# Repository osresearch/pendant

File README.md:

Bootloader
===

The ATtiny85 needs to be flashed with a bootloader before it can
be programmed with the Arduino IDE.  This requires extra hardware,
such as a teensy or arduino configured as an ISP.

The bootloader is then flashed via an SOIC socket.  It is possible to
via a chip clip, but this seems to be somewhat flakey due to the
charlieplexing matrix.

Using the arduino IDE, select "`File`-`Examples`-`11. Arduino ISP`"
and set the "`Tools`-`Board`" for whatever type of arduino or teensy you 
are using.  For a teensy the minimum pinout is:

	Teensy	SOIC	Use
	Vcc	8
	GND	4
	1	7	SCK
	2	5	MOSI
	3	6	MISO
	10	1	Reset

Clone the bootloader tree:

    git clone https://github.com/osresearch/gemma-bootloader

You might have to edit the `gemma-bootloader/Makefile` to have the
right path to your Arduino build environment and `avrdude` tool.  You will
likely have to edit it to set the serial device that your Teensy or
Arduino shows up as.

Connect the ArduinoISP to the ATtiny85 and flash the bootloader:

    make -C gemma-bootloader flash_lv

This should result in an ok message.  if it doesn't, check the connections
and try again.  If it is succesful you won't be able to reflash it,
since the reset pin is disabled.

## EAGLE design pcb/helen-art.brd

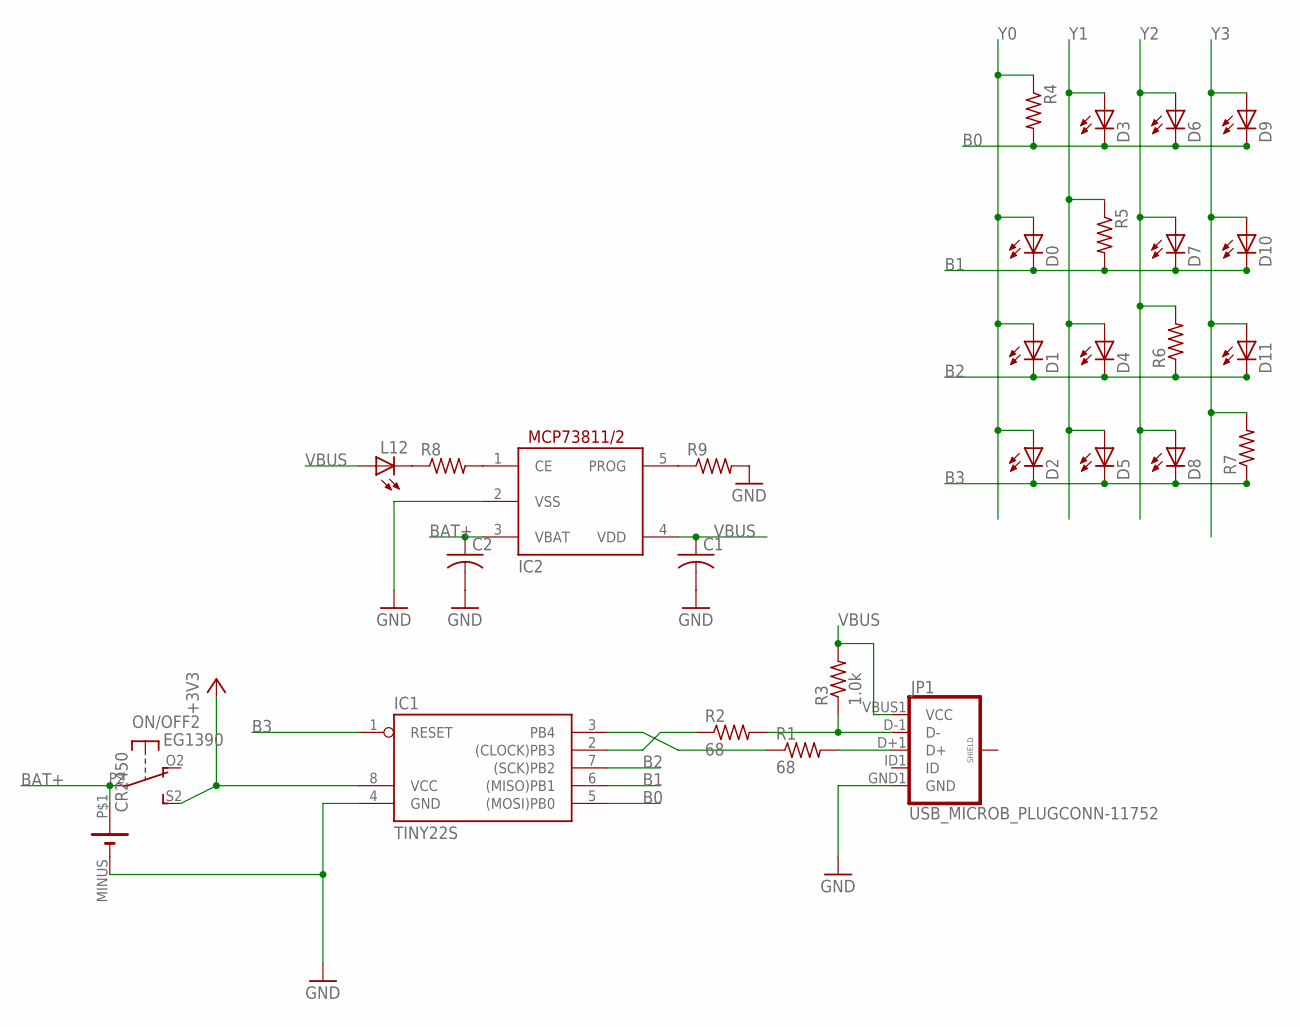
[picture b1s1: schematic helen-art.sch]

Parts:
C1, C2: C-USC0603; C0603
D0, D1, D2, D3, D4, D5, D6, D7, D8, D9, D10, D11: LEDCHIPLED_0805; CHIPLED_0805
IC1: TINY22S; SOIC8
IC2: MCP73811/2; SOT23-5L
JP1: USB_MICROB_PLUGCONN-11752; USB-B-MICRO-SMD_V03
L12: LEDCHIPLED_0805; CHIPLED_0805
ON/OFF: EG1390
R1, R2: 68; R0603
R3: 1.0k; R0603
R4, R5, R6, R7, R8, R9: R-US_R0603; R0603
U$3: CR2450; CR2450_KEYSTONE

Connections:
+3V3: IC1.8 (VCC), ON/OFF.S2 (S)
B0: D3.C, D6.C, D9.C, IC1.5 ((MOSI)PB0), R4.2
B1: D0.C, D7.C, D10.C, IC1.6 ((MISO)PB1), R5.2
B2: D1.C, D4.C, D11.C, IC1.7 ((SCK)PB2), R6.1
B3: D2.C, D5.C, D8.C, IC1.1 (RESET), R7.1
BAT+: C2.1, IC2.3 (VBAT), ON/OFF.P2, U$3.P$1 (+)
GND: C1.2, C2.2, IC1.4 (GND), IC2.2 (VSS), JP1.GND1 (GND), R9.2, U$3.MINUS (-)
unnamed: JP1.D+1 (D+), R1.2
unnamed: JP1.D-1 (D-), R2.2, R3.1
unnamed: IC1.3 (PB4), R1.1
unnamed: IC1.2 ((CLOCK)PB3), R2.1
unnamed: IC2.5 (PROG), R9.1
unnamed: IC2.1 (CE), R8.2
unnamed: L12.C, R8.1
VBUS: C1.1, IC2.4 (VDD), JP1.VBUS1 (VCC), L12.A, R3.2
Y0: D0.A, D1.A, D2.A, R4.1
Y1: D3.A, D4.A, D5.A, R5.1
Y2: D6.A, D7.A, D8.A, R6.2
Y3: D9.A, D10.A, D11.A, R7.2

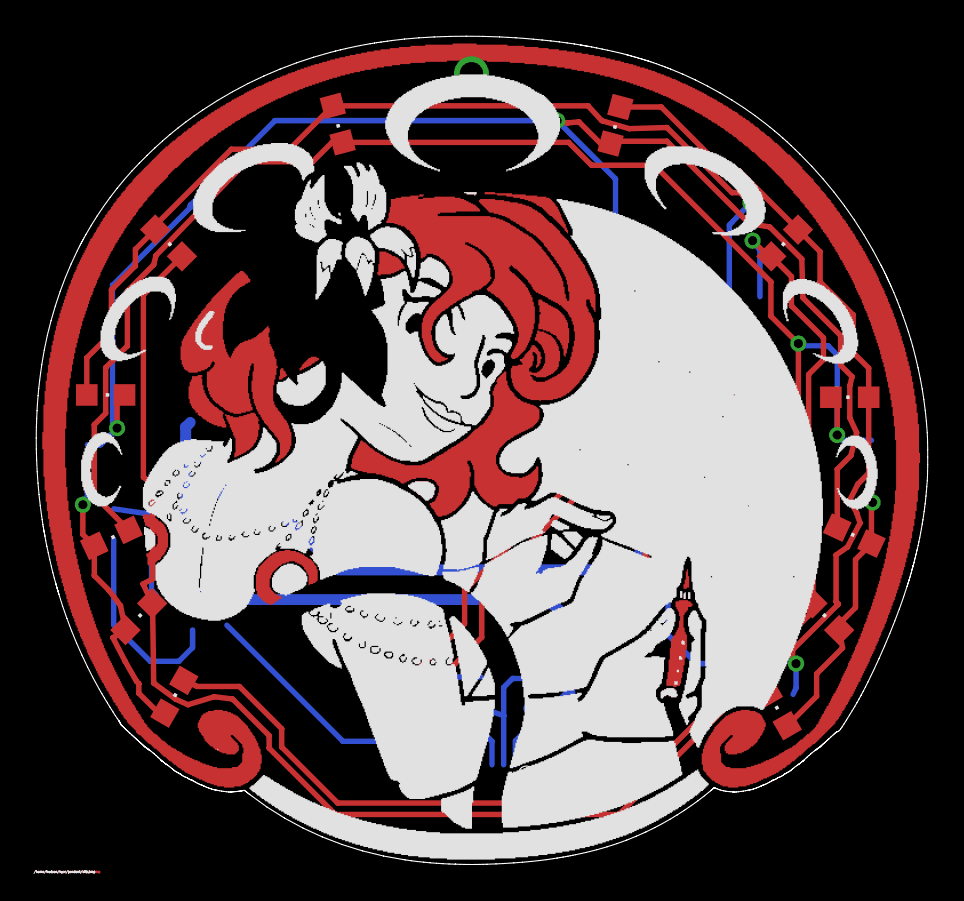
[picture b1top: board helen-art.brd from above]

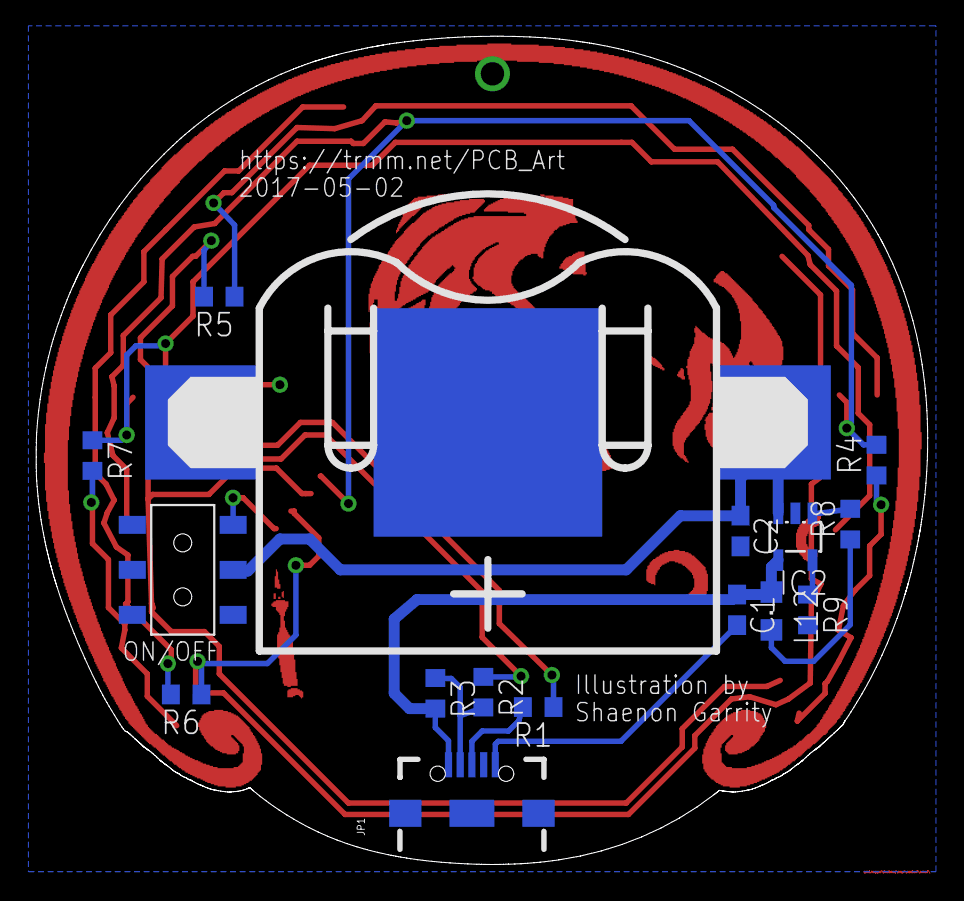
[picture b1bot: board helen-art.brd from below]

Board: 2 copper layers, 49.5 x 46.0 mm, 29 parts (16 on the bottom side), 19 nets.

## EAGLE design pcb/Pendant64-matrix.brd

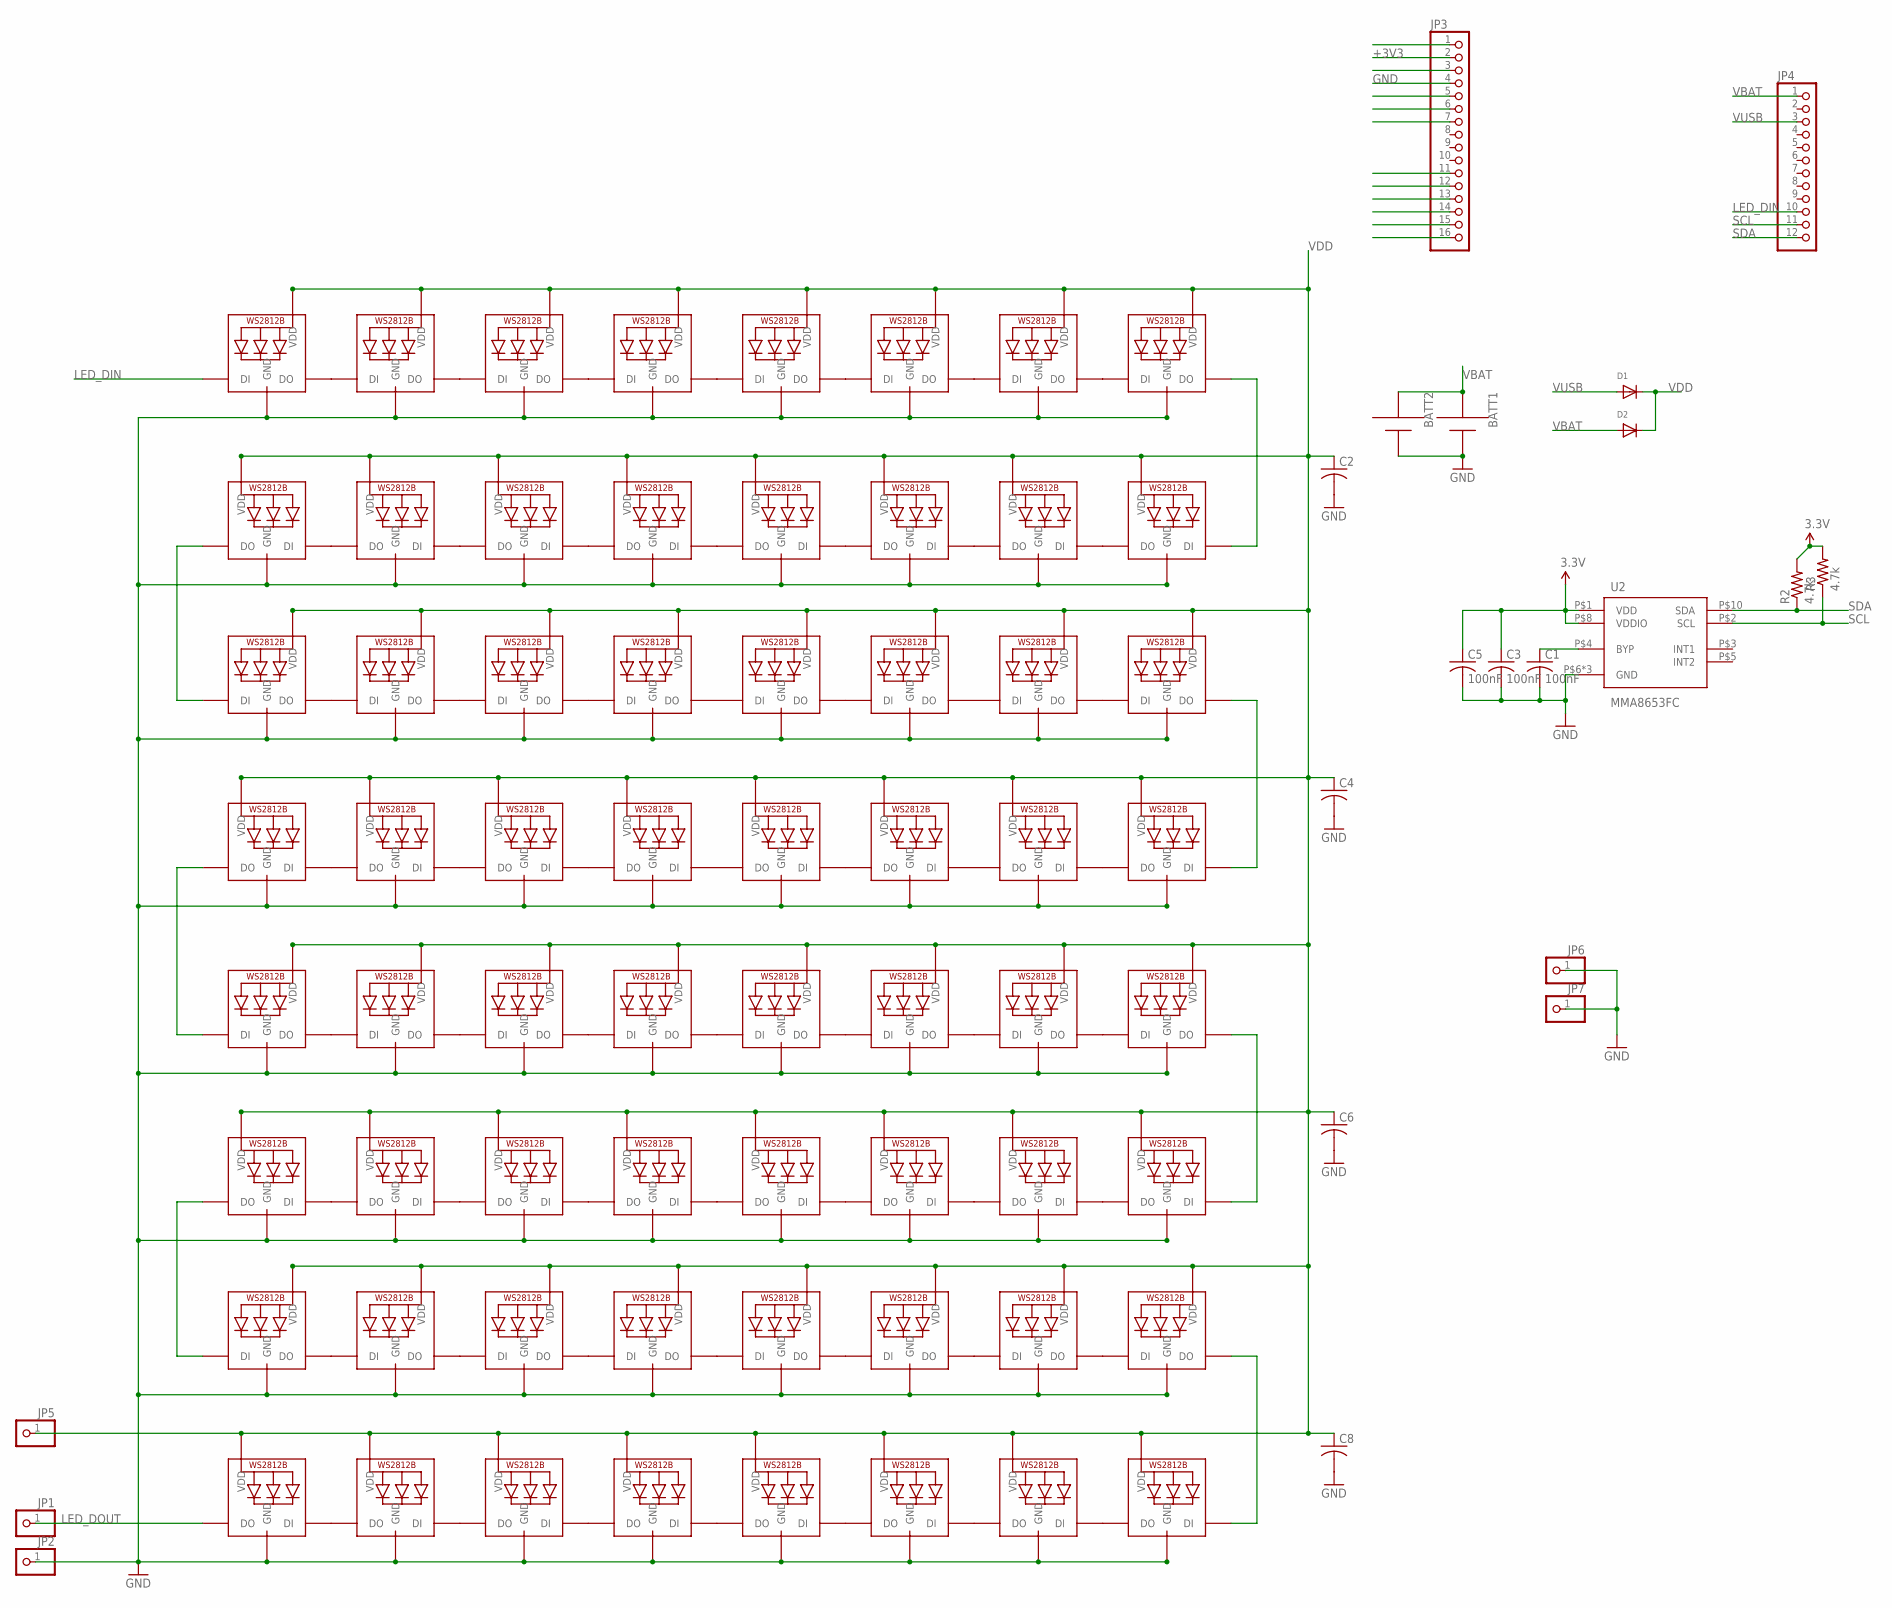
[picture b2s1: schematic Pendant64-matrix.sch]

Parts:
BATT1, BATT2: AAA; 12BH412
C1, C3, C5: 100nF; C0402
C2, C4, C6, C8: C-USC0402K; C0402K
D1, D2: DIODESOD-123; SOD-123
JP1, JP2, JP5, JP6, JP7: PINHD-1X1; 1X01
JP3: PINHD-1X161X16_SMT; 1X16_SMT
JP4: PINHD-1X121X12_SMT; 1X12_SMT
LED1, LED2, LED3, LED4, LED5, LED6, LED7, LED8, LED9, LED10, LED11, LED12, LED13, LED14, LED15, LED16, LED17, LED18, LED19, LED20, LED21, LED22, LED23, LED24, LED25, LED26, LED27, LED28, LED29, LED30, LED31, LED32, LED33, LED34, LED35, LED36, LED37, LED38, LED39, LED40, LED41, LED42, LED43, LED44, LED45, LED46, LED47, LED48, LED49, LED50, LED51, LED52, LED53, LED54, LED55, LED56, LED57, LED58, LED59, LED60, LED61, LED62, LED63, LED64: WS2812B3535; LED3535
R2, R3: 4.7k; R0402
U2: MMA8653FC; VFDFN-10

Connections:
+3V3: C3.1, C5.1, JP3.2, R2.2, R3.2, U2.P$1 (VDD), U2.P$8 (VDDIO)
GND: BATT1.+, BATT2.+, C1.2, C2.2, C3.2, C4.2, C5.2, C6.2, C8.2, JP2.1, JP3.4, JP6.1, JP7.1, LED1.4 (GND), LED2.4 (GND), LED3.4 (GND), LED4.4 (GND), LED5.4 (GND), LED6.4 (GND), LED7.4 (GND), LED8.4 (GND), LED9.4 (GND), LED10.4 (GND), LED11.4 (GND), LED12.4 (GND), LED13.4 (GND), LED14.4 (GND), LED15.4 (GND), LED16.4 (GND), LED17.4 (GND), LED18.4 (GND), LED19.4 (GND), LED20.4 (GND), LED21.4 (GND), LED22.4 (GND), LED23.4 (GND), LED24.4 (GND), LED25.4 (GND), LED26.4 (GND), LED27.4 (GND), LED28.4 (GND), LED29.4 (GND), LED30.4 (GND), LED31.4 (GND), LED32.4 (GND), LED33.4 (GND), LED34.4 (GND), LED35.4 (GND), LED36.4 (GND), LED37.4 (GND), LED38.4 (GND), LED39.4 (GND), LED40.4 (GND), LED41.4 (GND), LED42.4 (GND), LED43.4 (GND), LED44.4 (GND), LED45.4 (GND), LED46.4 (GND), LED47.4 (GND), LED48.4 (GND), LED49.4 (GND), LED50.4 (GND), LED51.4 (GND), LED52.4 (GND), LED53.4 (GND), LED54.4 (GND), LED55.4 (GND), LED56.4 (GND), LED57.4 (GND), LED58.4 (GND), LED59.4 (GND), LED60.4 (GND), LED61.4 (GND), LED62.4 (GND), LED63.4 (GND), LED64.4 (GND), U2.P$6 (GND), U2.P$7 (GND), U2.P$9 (GND)
LED_DIN: JP4.10, LED1.1 (DI)
LED_DOUT: JP1.1, LED64.3 (DO)
unnamed: LED1.3 (DO), LED2.1 (DI)
unnamed: LED2.3 (DO), LED3.1 (DI)
unnamed: LED3.3 (DO), LED4.1 (DI)
unnamed: LED4.3 (DO), LED5.1 (DI)
unnamed: LED5.3 (DO), LED6.1 (DI)
unnamed: LED6.3 (DO), LED7.1 (DI)
unnamed: LED7.3 (DO), LED8.1 (DI)
unnamed: LED9.3 (DO), LED10.1 (DI)
unnamed: LED10.3 (DO), LED11.1 (DI)
unnamed: LED11.3 (DO), LED12.1 (DI)
unnamed: LED12.3 (DO), LED13.1 (DI)
unnamed: LED13.3 (DO), LED14.1 (DI)
unnamed: LED14.3 (DO), LED15.1 (DI)
unnamed: LED15.3 (DO), LED16.1 (DI)
unnamed: LED17.3 (DO), LED18.1 (DI)
unnamed: LED18.3 (DO), LED19.1 (DI)
unnamed: LED19.3 (DO), LED20.1 (DI)
unnamed: LED20.3 (DO), LED21.1 (DI)
unnamed: LED21.3 (DO), LED22.1 (DI)
unnamed: LED22.3 (DO), LED23.1 (DI)
unnamed: LED23.3 (DO), LED24.1 (DI)
unnamed: LED25.3 (DO), LED26.1 (DI)
unnamed: LED26.3 (DO), LED27.1 (DI)
unnamed: LED27.3 (DO), LED28.1 (DI)
unnamed: LED28.3 (DO), LED29.1 (DI)
unnamed: LED29.3 (DO), LED30.1 (DI)
unnamed: LED30.3 (DO), LED31.1 (DI)
unnamed: LED31.3 (DO), LED32.1 (DI)
unnamed: LED33.3 (DO), LED34.1 (DI)
unnamed: LED34.3 (DO), LED35.1 (DI)
unnamed: LED8.3 (DO), LED9.1 (DI)
unnamed: LED16.3 (DO), LED17.1 (DI)
unnamed: LED24.3 (DO), LED25.1 (DI)
unnamed: LED32.3 (DO), LED33.1 (DI)
unnamed: LED35.3 (DO), LED36.1 (DI)
unnamed: LED36.3 (DO), LED37.1 (DI)
unnamed: LED37.3 (DO), LED38.1 (DI)
unnamed: LED38.3 (DO), LED39.1 (DI)
unnamed: LED39.3 (DO), LED40.1 (DI)
unnamed: LED41.3 (DO), LED42.1 (DI)
unnamed: LED42.3 (DO), LED43.1 (DI)
unnamed: LED43.3 (DO), LED44.1 (DI)
unnamed: LED44.3 (DO), LED45.1 (DI)
unnamed: LED45.3 (DO), LED46.1 (DI)
unnamed: LED46.3 (DO), LED47.1 (DI)
unnamed: LED47.3 (DO), LED48.1 (DI)
unnamed: LED49.3 (DO), LED50.1 (DI)
unnamed: LED50.3 (DO), LED51.1 (DI)
unnamed: LED51.3 (DO), LED52.1 (DI)
unnamed: LED52.3 (DO), LED53.1 (DI)
unnamed: LED53.3 (DO), LED54.1 (DI)
unnamed: LED54.3 (DO), LED55.1 (DI)
unnamed: LED55.3 (DO), LED56.1 (DI)
unnamed: LED57.3 (DO), LED58.1 (DI)
unnamed: LED58.3 (DO), LED59.1 (DI)
unnamed: LED59.3 (DO), LED60.1 (DI)
unnamed: LED60.3 (DO), LED61.1 (DI)
unnamed: LED61.3 (DO), LED62.1 (DI)
unnamed: LED62.3 (DO), LED63.1 (DI)
unnamed: LED63.3 (DO), LED64.1 (DI)
unnamed: C1.1, U2.P$4 (BYP)
unnamed: LED40.3 (DO), LED41.1 (DI)
unnamed: LED48.3 (DO), LED49.1 (DI)
unnamed: LED56.3 (DO), LED57.1 (DI)
SCL: JP4.11, R3.1, U2.P$2 (SCL)
SDA: JP4.12, R2.1, U2.P$10 (SDA)
VBAT: BATT1.-, BATT2.-, D2.A, JP4.1
VDD: C2.1, C4.1, C6.1, C8.1, D1.C, D2.C, JP5.1, LED1.2 (VDD), LED2.2 (VDD), LED3.2 (VDD), LED4.2 (VDD), LED5.2 (VDD), LED6.2 (VDD), LED7.2 (VDD), LED8.2 (VDD), LED9.2 (VDD), LED10.2 (VDD), LED11.2 (VDD), LED12.2 (VDD), LED13.2 (VDD), LED14.2 (VDD), LED15.2 (VDD), LED16.2 (VDD), LED17.2 (VDD), LED18.2 (VDD), LED19.2 (VDD), LED20.2 (VDD), LED21.2 (VDD), LED22.2 (VDD), LED23.2 (VDD), LED24.2 (VDD), LED25.2 (VDD), LED26.2 (VDD), LED27.2 (VDD), LED28.2 (VDD), LED29.2 (VDD), LED30.2 (VDD), LED31.2 (VDD), LED32.2 (VDD), LED33.2 (VDD), LED34.2 (VDD), LED35.2 (VDD), LED36.2 (VDD), LED37.2 (VDD), LED38.2 (VDD), LED39.2 (VDD), LED40.2 (VDD), LED41.2 (VDD), LED42.2 (VDD), LED43.2 (VDD), LED44.2 (VDD), LED45.2 (VDD), LED46.2 (VDD), LED47.2 (VDD), LED48.2 (VDD), LED49.2 (VDD), LED50.2 (VDD), LED51.2 (VDD), LED52.2 (VDD), LED53.2 (VDD), LED54.2 (VDD), LED55.2 (VDD), LED56.2 (VDD), LED57.2 (VDD), LED58.2 (VDD), LED59.2 (VDD), LED60.2 (VDD), LED61.2 (VDD), LED62.2 (VDD), LED63.2 (VDD), LED64.2 (VDD)
VUSB: D1.A, JP4.3

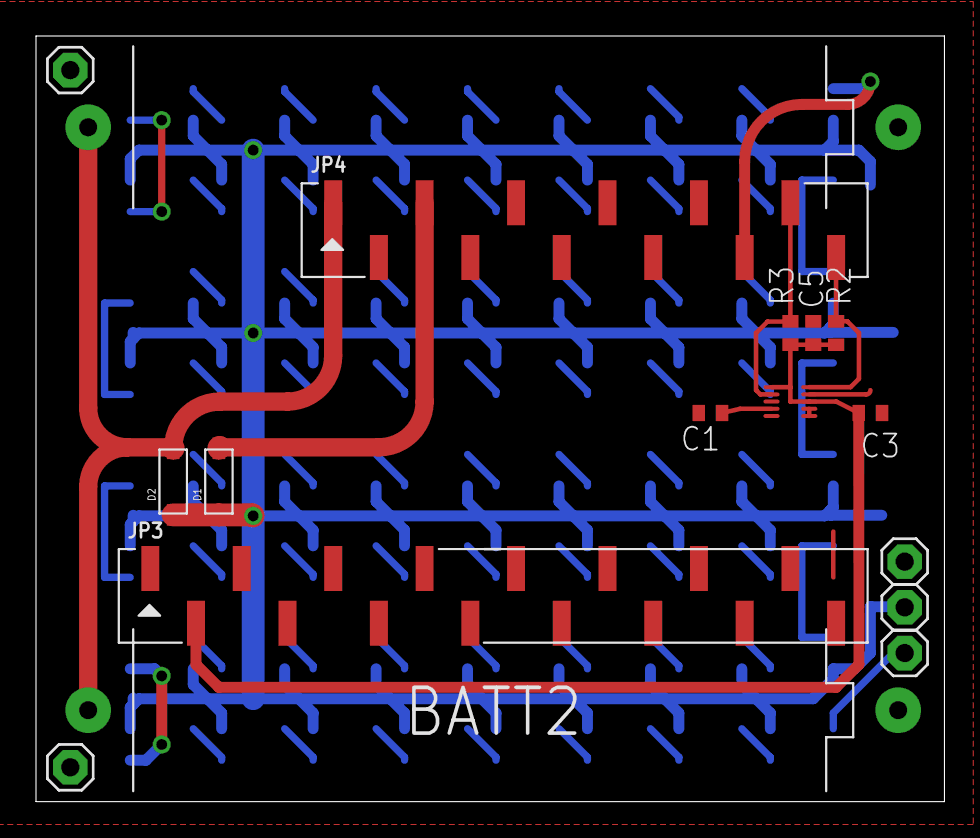
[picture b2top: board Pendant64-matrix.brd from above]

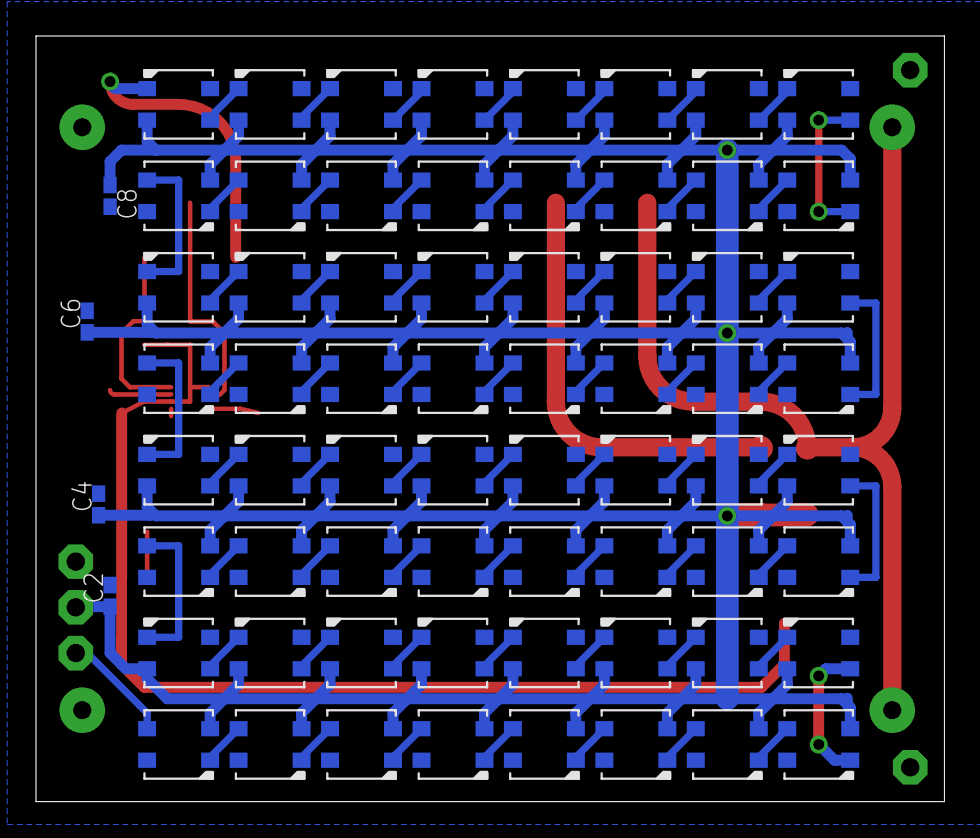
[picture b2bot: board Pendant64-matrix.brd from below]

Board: 2 copper layers, 50.5 x 42.5 mm, 85 parts (68 on the bottom side), 73 nets.

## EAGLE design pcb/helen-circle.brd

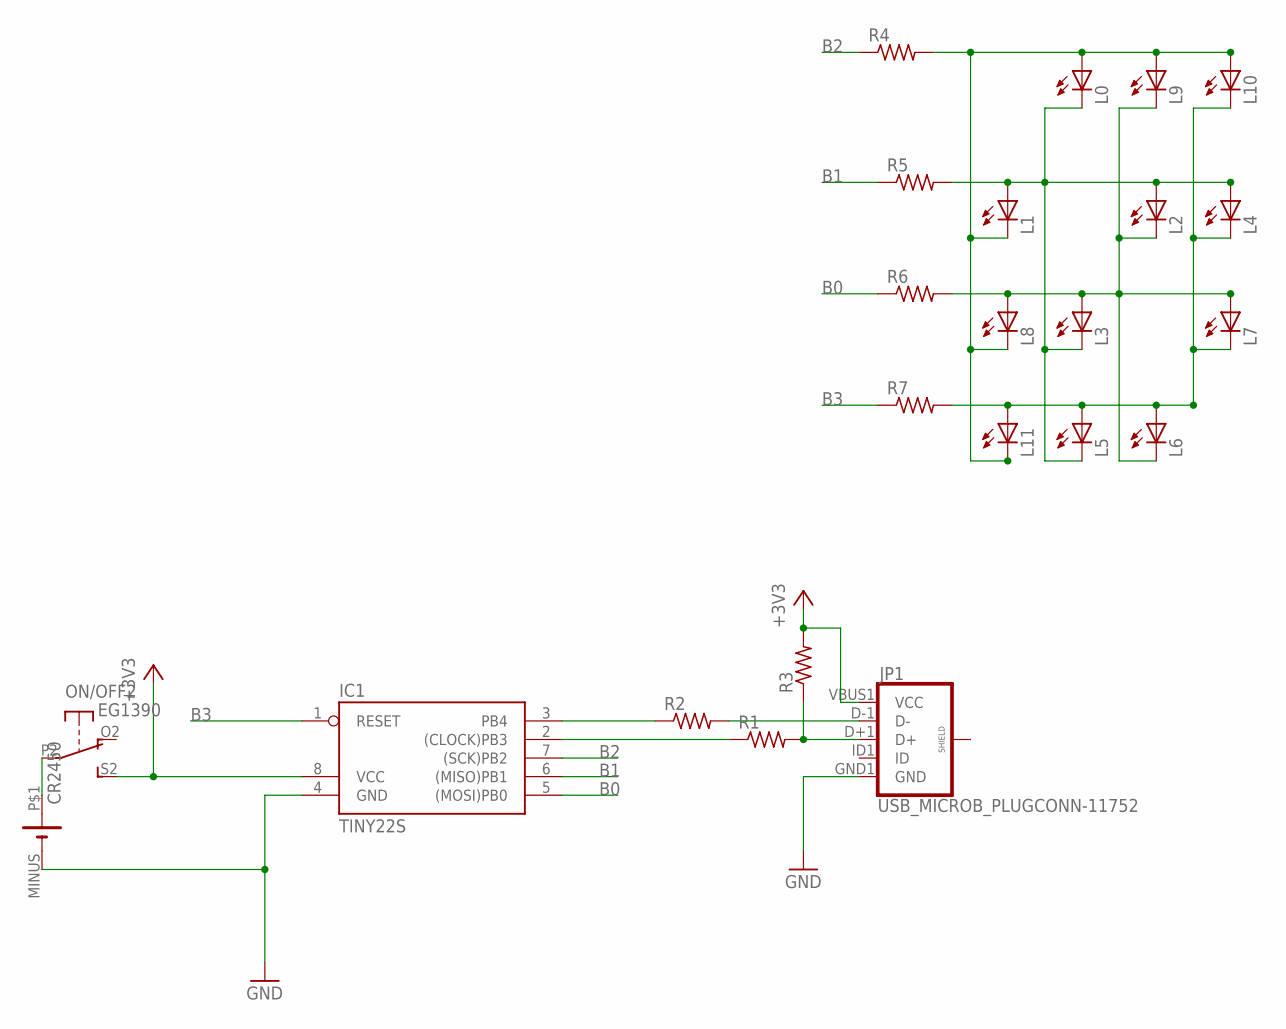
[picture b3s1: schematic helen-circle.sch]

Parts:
IC1: TINY22S; SOIC8
JP1: USB_MICROB_PLUGCONN-11752; USB-B-MICRO-SMD_V03
L0, L1, L2, L3, L4, L5, L6, L7, L8, L9, L10, L11: LEDCHIPLED_0805; CHIPLED_0805
ON/OFF: EG1390
R1, R2, R3, R4, R5, R6, R7: R-US_R0603; R0603
U$3: CR2450; CR2450_KEYSTONE

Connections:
+3V3: IC1.8 (VCC), JP1.VBUS1 (VCC), ON/OFF.S2 (S), R3.2
B0: IC1.5 ((MOSI)PB0), R6.1
B0': L2.C, L3.A, L6.C, L7.A, L8.A, L9.C, R6.2
B1: IC1.6 ((MISO)PB1), R5.1
B1': L0.C, L1.A, L2.A, L3.C, L4.A, L5.C, R5.2
B2: IC1.7 ((SCK)PB2), R4.1
B2': L0.A, L1.C, L8.C, L9.A, L10.A, L11.C, R4.2
B3: IC1.1 (RESET), R7.1
B3': L4.C, L5.A, L6.A, L7.C, L10.C, L11.A, R7.2
GND: IC1.4 (GND), JP1.GND1 (GND), U$3.MINUS (-)
unnamed: JP1.D+1 (D+), R1.2, R3.1
unnamed: JP1.D-1 (D-), R2.2
unnamed: IC1.2 ((CLOCK)PB3), R1.1
unnamed: IC1.3 (PB4), R2.1
unnamed: ON/OFF.P2, U$3.P$1 (+)

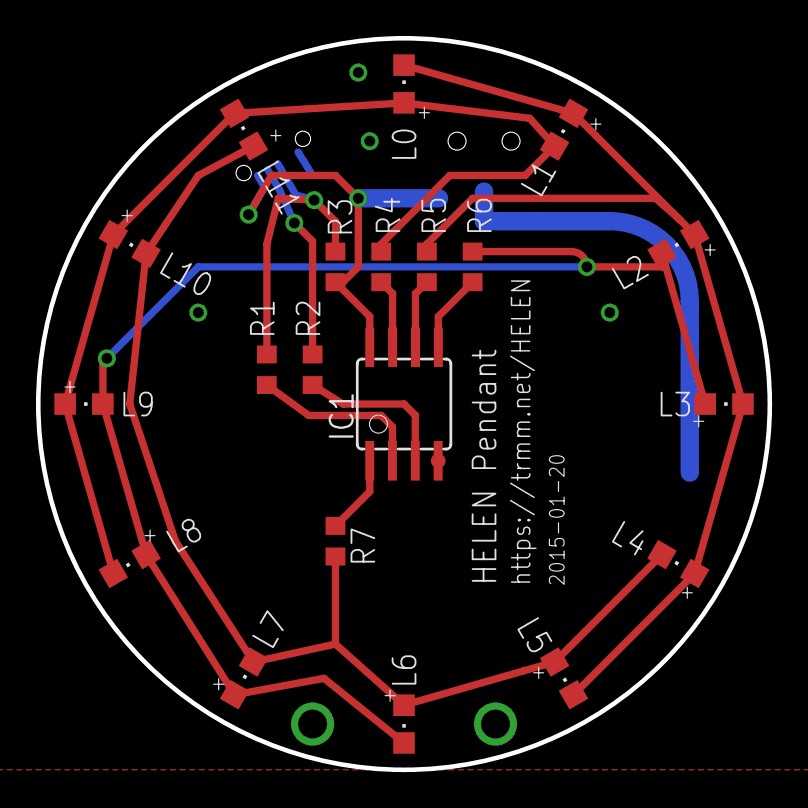
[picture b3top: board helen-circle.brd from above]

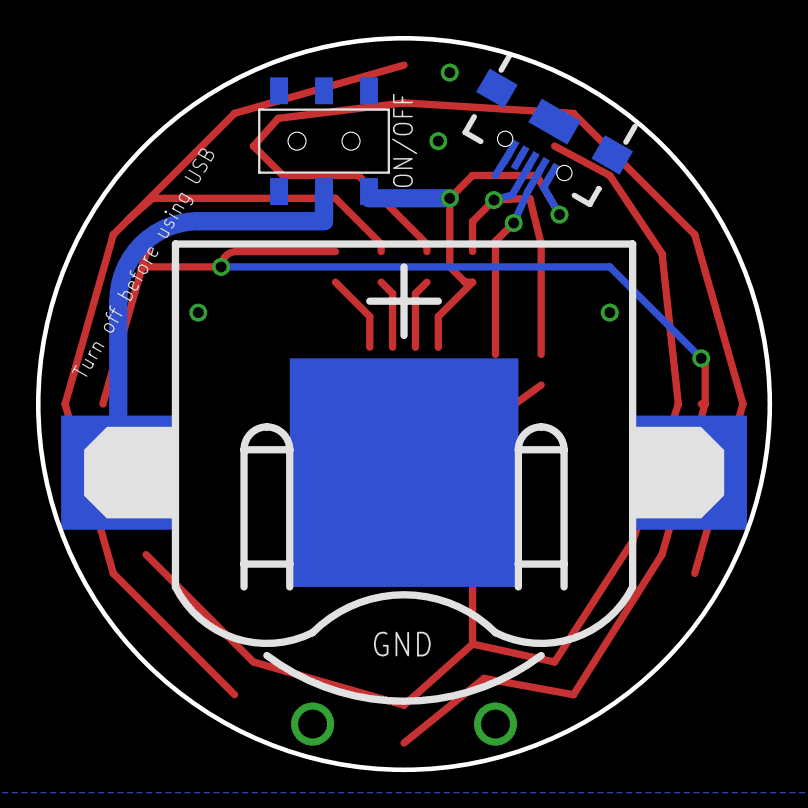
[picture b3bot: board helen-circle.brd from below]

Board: 2 copper layers, 40.6 x 40.6 mm, 23 parts (3 on the bottom side), 15 nets.

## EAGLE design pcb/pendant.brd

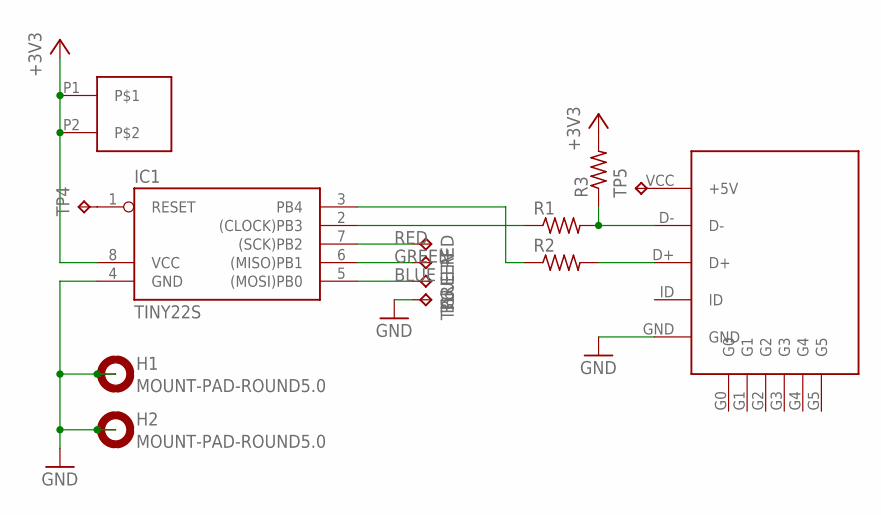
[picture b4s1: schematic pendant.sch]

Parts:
BLUE: TPPAD1-13; P1-13
GREEN: TPPAD1-13; P1-13
H1, H2: MOUNT-PAD-ROUND5.0; 5,0-PAD
IC1: TINY22S; SOIC8
R1, R2, R3: R-US_R0603; R0603
RED: TPPAD1-13; P1-13
TP4, TP6: TPPAD1-13; P1-13
TP5: TPTP10SQ; TP10SQ
U$1: USB-MICRO; UB-MC5BR3-M404
U$2: MAGNET8TH-INCH; 8TH-SQUARE

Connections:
+3V3: IC1.8 (VCC), R3.2, U$2.P1, U$2.P2
BLUE: BLUE.TP, IC1.5 ((MOSI)PB0)
G0: U$1.G0
G1: U$1.G1
G2: U$1.G2
G3: U$1.G3
G4: U$1.G4
G5: U$1.G5
GND: H1.B5, H2.B5, IC1.4 (GND), TP6.TP, U$1.GND
GREEN: GREEN.TP, IC1.6 ((MISO)PB1)
unnamed: R1.2, R3.1, U$1.D-
unnamed: R2.2, U$1.D+
unnamed: IC1.2 ((CLOCK)PB3), R1.1
unnamed: IC1.3 (PB4), R2.1
unnamed: IC1.1 (RESET), TP4.TP
unnamed: TP5.TP, U$1.VCC (+5V)
RED: IC1.7 ((SCK)PB2), RED.TP

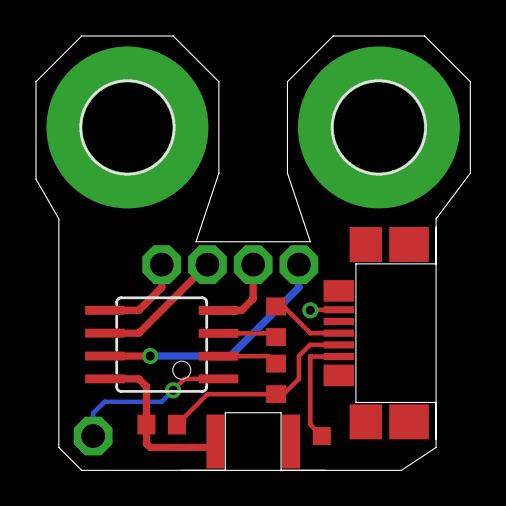
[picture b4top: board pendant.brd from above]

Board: 2 copper layers, 24.1 x 24.1 mm, 14 parts (0 on the bottom side), 11 nets.

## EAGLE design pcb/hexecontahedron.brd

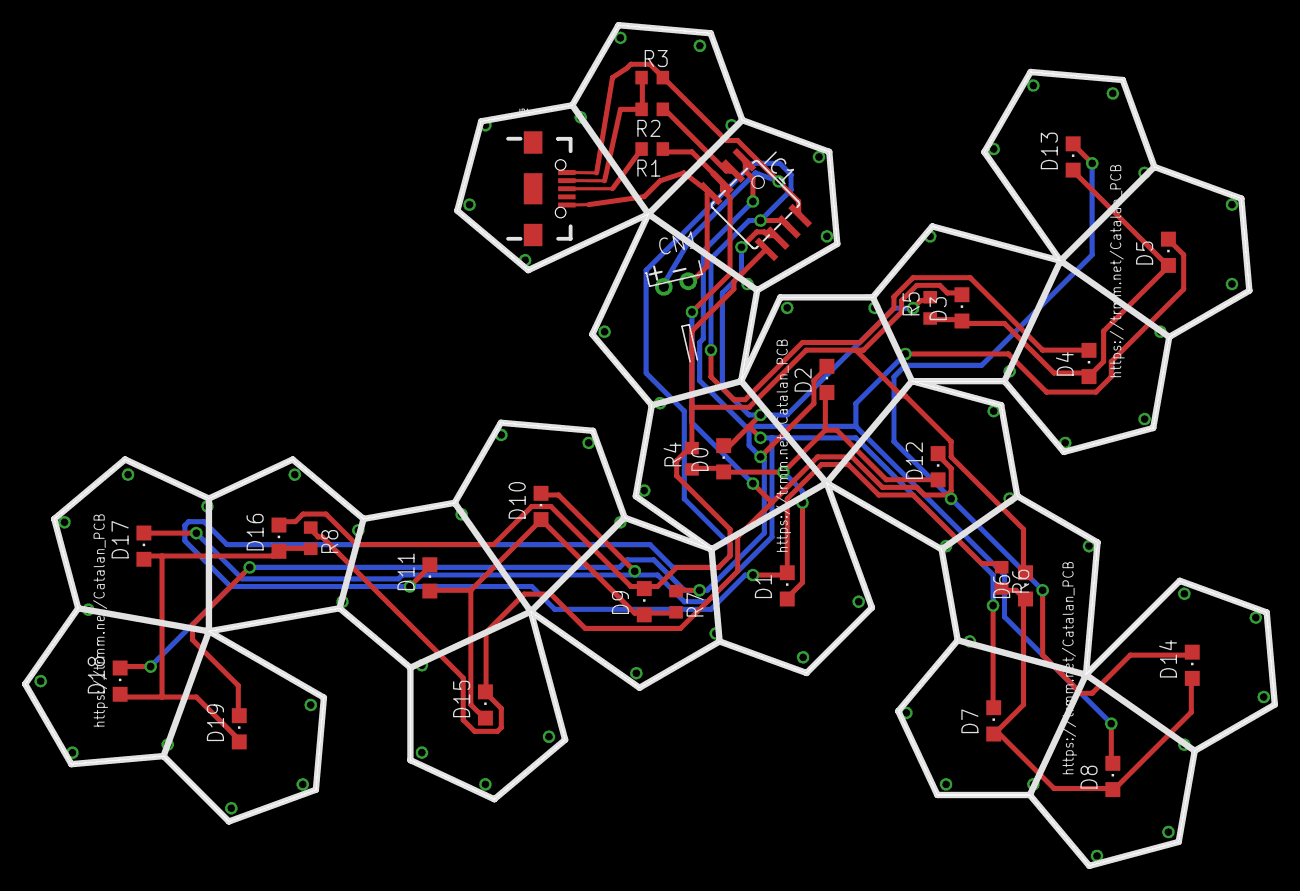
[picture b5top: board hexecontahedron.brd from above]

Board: 2 copper layers, 99.9 x 67.2 mm, 31 parts (0 on the bottom side), 15 nets.

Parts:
CN1: JST-PH-2-THM-RA
D0, D1, D2, D3, D4, D5, D6, D7, D8, D9, D10, D11, D12, D13, D14, D15, D16, D17, D18, D19: CHIPLED_0805
IC1: TINY22S; SOIC8
JP1: USB_MICROB_PLUGCONN-11752; USB-B-MICRO-SMD_V03
R1, R2: 68; R0603
R3: 1.0k; R0603
R4, R5, R6, R7, R8: R0603

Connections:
B0: D3.C, D6.C, D9.C, D16.C, IC1.5, R4.2
B1: D0.C, D7.C, D10.C, D17.C, IC1.6, R5.2
B2: D1.C, D4.C, D11.C, D18.C, IC1.7, R6.1
B3: D2.C, D5.C, D8.C, D19.C, IC1.1, R7.1
B4: D12.C, D13.C, D14.C, D15.C, IC1.3, R1.1, R8.1
GND: CN1.2, IC1.4, JP1.GND1
unnamed: JP1.D+1, R1.2
unnamed: JP1.D-1, R2.2, R3.1
unnamed: IC1.2, R2.1
VBUS: CN1.1, IC1.8, JP1.VBUS1, R3.2
Y0: D0.A, D1.A, D2.A, D12.A, R4.1
Y1: D3.A, D4.A, D5.A, D13.A, R5.1
Y2: D6.A, D7.A, D8.A, D14.A, R6.2
Y3: D9.A, D10.A, D11.A, D15.A, R7.2
Y4: D16.A, D17.A, D18.A, D19.A, R8.2

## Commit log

2014-07-13 pendant color cycle works
2014-07-13 cycle through a palette array
2014-07-13 better colors, all off
2014-07-13 avrispmkii program command
2014-07-16 import of pcb and micro-usb
2014-07-17 added square cutout magnet, worked on board outline
2014-07-17 switch to 8th-inch magnet
2014-07-17 fix usb wiring bug; fully routed
2014-07-29 port code to arduino and common cathode for new board
2014-08-06 random fixes for common cathode
2014-08-10 neopixel based pendant instead
2014-08-15 more colors!
2014-08-15 slow update rate
2014-08-15 slow the clock to 2 MHz
2014-08-16 use deep sleep and the wdt to wake up
2015-01-19 circular pendant with 12 LEDs
2015-02-02 import of trinketloader
2015-02-08 working loader for helen board
2015-02-08 import of charlie plexing thing
2015-02-08 laser cut face for helen circle board
2015-02-08 speed up loader output
2015-02-08 chase 2 things around
2015-02-09 two more patterns
2015-02-09 better twinkle
2015-02-10 deep sleep; save the battery
2015-02-10 wdt does not wake up?
2016-03-25 import from esp8266 tree
2016-03-25 packet exchange seems to work
2016-03-25 leader/follower wifi connections work
2016-03-25 adding some new led patterns for scanning and following mode
2016-03-26 rearrange to work with arduino 1.6.7
2016-03-26 move some of the color processing code into its own file
2016-03-26 merged
2016-03-26 adding patterns for scanning and other modes. Only scanning mode pattern is unique in this version.
2016-03-26 define network packet, put colors in it
2016-03-26 moving pixel pattern code above wifi protocol code for the modes, so that the wifi functions can call the patter functions. Plus follower should now display its leaders color.
2016-03-26 leader color flashing in follower mode, which follower color successful pulses its color. Need more sustain leader color
2016-03-26 refactoring follower state so now blinks leaders color on packet reception, with color fading as packet ages
2016-03-26 leader and candidate patterns decay with beacon age to match follower
2016-03-28 8x8 addressable matrix with feather wing board and accelerometer on the back
2016-03-28 added a second AAA battery, relocated wifi to center of board
2016-04-09 does not work -- but about to make it worse. adding leader code.
2016-04-10 works now. patterns need some tweaking. Leader should emty array space sooner when it loses beacons from followers.
2016-04-10 Fixing broadcast of leader packets so they are received by followers.
2016-04-10 followers now return to scanning once they're lost their leader
2016-04-12 shortening rescan interval, follower now pulses self color when it sends a packet, leader relinquishes leds for lost followers
2016-04-14 adding support for a color assignment message from the leader, it compiles, but the code for the follower to accept the assignment isn't in place yet so unsure if it works
2016-04-14 color assignmest from leader to follower are now working, but wifi protocol is no longer stable so leaders quickly revert to scanning after attaining a follower.
2016-04-14 fixing one obvious bug where it was claiming the used_colors array was full if one slot was empty, still not acquiring followers.
2016-04-15 removing infinite loop, but followers are still getting errors when trying to join. Next step: moving some of the color assignment code out into a function to make debugging easier.
2016-04-15 removing the test for previously used random colors, and just making color assignment to followers only random to ease debugging
2016-04-15 working now! One magical line of code stabilizes connections: WiFi.persistant(false), and followers can connect to leaders now. Still not keeping track of used colors, just picking randomly from the 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
2016-04-17 adding a delay when drawing LEDs to try to help leaders hear followers who are trying to connect. seems to help a little
2017-05-03 ignore eagle temp files
2017-05-03 parts placed and routed
2017-05-03 fix D+/D- swap and remove LED labels
2017-05-03 text on the back, ready to order
2017-05-03 svg of the artwork
2017-05-12 values for resistors
2017-05-16 board without any artwork
2017-05-19 use one pattern
2017-05-19 union mask and silk layer to avoid oshpark error
2017-05-19 no more clearance issues
2017-05-19 remove a few copper bits
2017-05-19 add image back in
2017-05-19 updates for teensy and arduino 1.6.11
2017-05-31 successful build and install
2017-11-24 updates for 20 output boards
2017-12-18 flexible Catalan hexecontahedron PCB

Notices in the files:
parts and their libraries:
SparkFun-Aesthetics: Licensing: CC v3.0 Share-Alike You are welcome to use this library for commercial purposes.
SparkFun-Connectors: Licensing: Creative Commons ShareAlike 4.0 International - https://creativecommons.org/licenses/by-sa/4.0
